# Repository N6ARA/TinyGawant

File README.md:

# TinyGawant

TinyGawant Antenna Project - A minature QRP antenna with a built-in tuner and SWR indicator.

[N6ARA Product Page - TinyGawant](https://n6ara.com/product/tinygawant-kit/)

# Build

## Board Files

See Gerber Files in [PCB/TinyGawant](/PCB/TinyGawant) Folder

## Bill of Materials

See [BOM](/BOM) Folder

## 3D Print Files

See [3D Printables](/3D%20Printables/) Folder

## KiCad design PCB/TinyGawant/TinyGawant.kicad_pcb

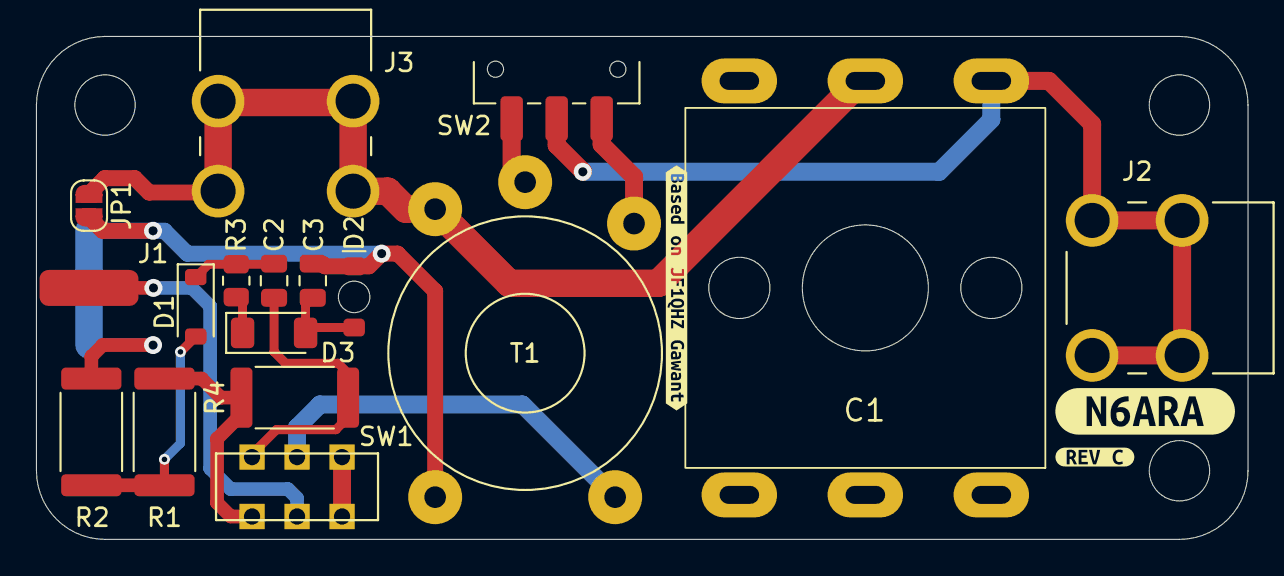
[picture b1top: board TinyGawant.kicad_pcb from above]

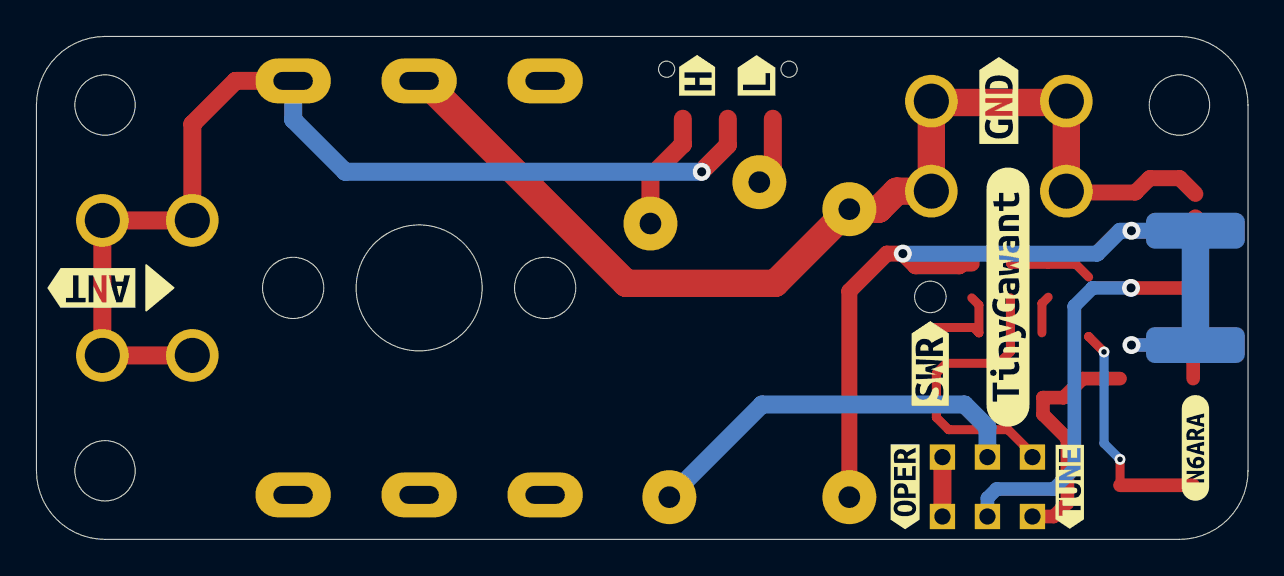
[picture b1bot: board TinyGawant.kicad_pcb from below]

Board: 2 copper layers, 67.3 x 27.9 mm, 29 parts (9 on the bottom side), 14 nets.

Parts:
C1: Polyvaricon_Capacitor
C2, C3: 0.01; C_0805_2012Metric
D1: 750-CDBW46-G; D_SOD-123
D2: RED; WL-SMRD-Bottom-Mount
D3: TZMC3V3-GS08; D_MiniMELF
J1: Conn_Coaxial; BNC_Edge
J2, J3: 7695-3; KEYSTONE_7695-3
JP1: Jumper_2_Bridged; SolderJumper-2_P1.3mm_Open_RoundedPad1.0x1.5mm
R1, R2, R4: 50; R_2512_6332Metric
R3: 1k; R_0805_2012Metric
SW1: SW_DPDT_x2; JS202011AQN
SW2: SW_SPDT; SW_SPDT_CK_JS102011SAQN
T1: Transformer_1P_SS; Transformer_Toroid_Horizontal_D14.0mm_Amidon-T50_3_2
kibuzzard-675A8744: G***; kibuzzard-675A8744
kibuzzard-676A6A04: G***; kibuzzard-676A6A04
kibuzzard-6922A9F4: G***; kibuzzard-6922A9F4
kibuzzard-6923ECB0: G***; kibuzzard-6923ECB0
kibuzzard-6923ED1D: G***; kibuzzard-6923ED1D
kibuzzard-6923F3E6: G***; kibuzzard-6923F3E6
kibuzzard-6923F404: G***; kibuzzard-6923F404
kibuzzard-677780D3: G***; kibuzzard-677780D3
kibuzzard-692298D5: G***; kibuzzard-692298D5
kibuzzard-692298E1: G***; kibuzzard-692298E1
kibuzzard-67778075: G***; kibuzzard-67778075
kibuzzard-69227399: G***; kibuzzard-69227399

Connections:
GND: C3.2, D2.1 (K), J1.2 (Ext), JP1.2 (B), R2.2, T1.1 (AA)
unnamed: D1.2 (A), R1.2, R2.1
unnamed: C2.2, D1.1 (K), R3.1
unnamed: C3.1, D2.2 (A), D3.2 (A)
unnamed: D3.1 (K), R3.2
unnamed: J1.1 (In), SW1.2 (B)
unnamed: C1.4, J2.1, J2.2 (1__1), J2.3 (1__2), J2.4 (1__3), SW2.2 (B)
unnamed: R1.1, R4.2, SW1.1 (A)
unnamed: SW1.3 (C), SW1.6 (C)
unnamed: C2.1, R4.1, SW1.4 (A)
unnamed: SW1.5 (B), T1.2 (AB)
unnamed: SW2.1 (A), T1.4 (SC)
unnamed: SW2.3 (C), T1.3 (SA)
RFGND: C1.2, C1.5, J3.1, J3.2 (1__1), J3.3 (1__2), J3.4 (1__3), JP1.1 (A), T1.5 (SB)

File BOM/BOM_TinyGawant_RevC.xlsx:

Reference | Value | Qty | MPN | Cost | Link
C2,C3 | 0.01 | 2 | GMC21X7R103J50NT | 0.2 | Digikey Cart
D1 | 750-CDBW46-G | 1 | CDBW46-G | 0.26 | Digikey Cart
D2 | RED | 1 | 156125RS57000 | 0.42 | Digikey Cart
D3 | TZMC3V3-GS08 | 1 | TZMC3V3-GS08 | 0.13 | Digikey Cart
J2,J3 | 7695-3 | 2 | 7790 | 1.28 | Digikey Cart
R1,R2,R4 | 50 | 3 | CRM2512-FX-51R0ELF | 1.56 | Digikey Cart
R3 | 1k | 1 | RC0805FR-071KL | 0.12 | Digikey Cart
SW1 | SW_DPDT_x2 | 1 | JS202011AQN | 0.75 | Digikey Cart
SW2 | SW_SPDT | 1 | JS102011SAQN | 0.76 | Digikey Cart
C1 |  | 1 | CBM-443BF | 2 | https://www.aliexpress.us/item/2255800609195661.html?spm=a2g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
T1 |  | 1 | T50-6 | 1.57 | https://www.amidoncorp.com/t50-6/
J1 |  | 1 | BNC Thru Hole Plug male Vertical PCB Mount Straight RF Coax ADAPTER | 1 | https://www.aliexpress.us/item/2251832111232237.html?spm=a2g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
PCB |  | 1 | JLCPCB | 1
Red Wire |  |  |  | 0.1
Green Wire |  |  |  | 0.1
Antenna |  | 1 | M3 Male Thread Screw On Telescopic Antenna 7 Sections 97.3CM | 1.8759999999999999 | https://www.aliexpress.us/item/2251832701726364.html?spm=a2g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
Thumb Screw |  | 1 | M3x6mm(DXL) Knurled Thumb Screws | 0.9 | https://www.amazon.com/dp/B0BZRM6ZYM?ref_=ppx_hzsearch_conn_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
M2.5x10mm |  | 1 | M2.5x10mm | 0.1 | https://www.amazon.com/iexcell-Thread-Stainless-Socket-Screw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
M2.5x6mm |  | 2 | M2.5x6mm | 0.2 | https://www.amazon.com/iexcell-Thread-Stainless-Socket-Screw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
M3 x 12mm |  | 3 | M3 x 12mm | 0.30000000000000004 | https://www.amazon.com/iexcell-Thread-Stainless-Socket-Screw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
Total |  |  |  | 14.625999999999999

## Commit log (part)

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2025-12-20 Initial Commit - Production Rev C
2025-12-20 added super basic instructions
2026-02-09 Update to Rev C Production
